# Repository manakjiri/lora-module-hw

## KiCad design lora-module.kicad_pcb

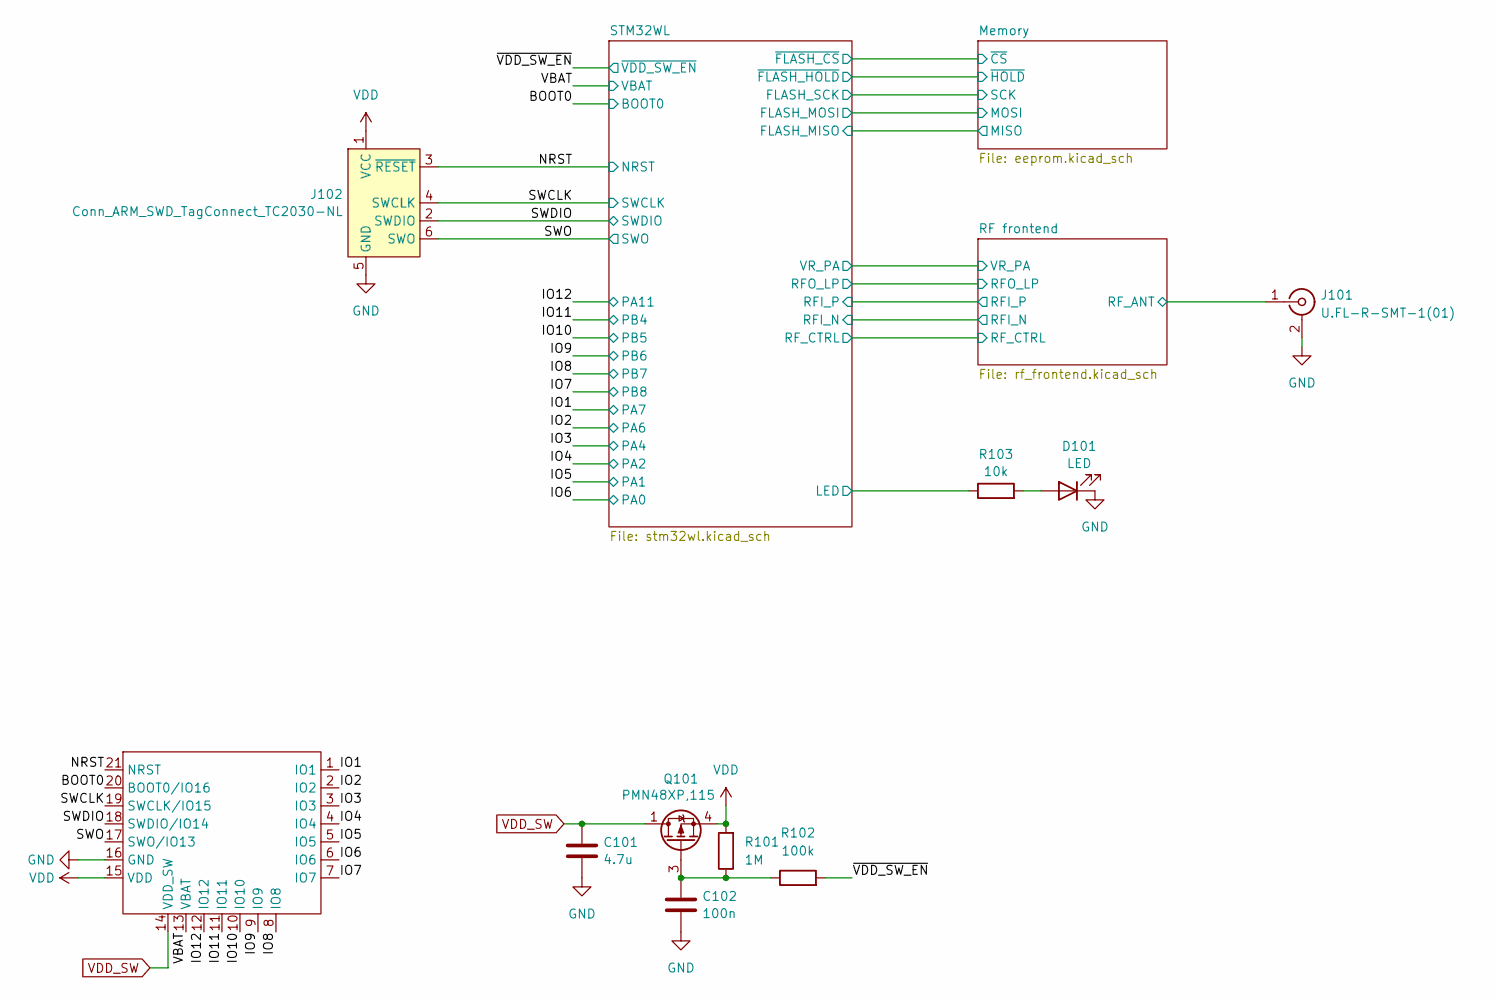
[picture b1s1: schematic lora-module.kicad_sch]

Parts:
C101: 4.7u; C_0603_1608Metric
C102: 100n; C_0402_1005Metric
D101: LED; LED_0402_1005Metric
J101: U.FL-R-SMT-1(01); U.FL_Hirose_U.FL-R-SMT-1_Vertical
J102: Conn_ARM_SWD_TagConnect_TC2030-NL; Tag-Connect_TC2030-IDC-NL_2x03_P1.27mm_Vertical
J106: module-connectors
Q101: PMN48XP,115; TSOP-6_1.65x3.05mm_P0.95mm
R101: 1M; R_0402_1005Metric
R102: 100k; R_0402_1005Metric
R103: 10k; R_0402_1005Metric

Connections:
/BOOT0: J106.20 (BOOT0/IO16); also elsewhere on the board
/IO1: J106.1 (IO1); also elsewhere on the board
/IO2: J106.2 (IO2); also elsewhere on the board
/IO3: J106.3 (IO3); also elsewhere on the board
/IO4: J106.4 (IO4); also elsewhere on the board
/IO5: J106.5 (IO5); also elsewhere on the board
/IO6: J106.6 (IO6); also elsewhere on the board
/IO7: J106.7 (IO7); also elsewhere on the board
/IO8: J106.8 (IO8); also elsewhere on the board
/IO9: J106.9 (IO9); also elsewhere on the board
/IO10: J106.10 (IO10); also elsewhere on the board
/IO11: J106.11 (IO11); also elsewhere on the board
/IO12: J106.12 (IO12); also elsewhere on the board
/NRST: J102.3 (~RESET), J106.21 (NRST); also elsewhere on the board
/RF frontend/RF_ANT: J101.1 (In); also elsewhere on the board
/STM32WL/LED: R103.1; also elsewhere on the board
/SWCLK: J102.4 (SWCLK), J106.19 (SWCLK/IO15); also elsewhere on the board
/SWDIO: J102.2 (SWDIO), J106.18 (SWDIO/IO14); also elsewhere on the board
/SWO: J102.6 (SWO), J106.17 (SWO/IO13); also elsewhere on the board
/VBAT: J106.13 (VBAT); also elsewhere on the board
/~VDD_SW_EN: R102.2; also elsewhere on the board
GND: C101.2, C102.2, D101.1 (K), J101.2 (Ext), J102.5 (GND), J106.16 (GND); also elsewhere on the board
unnamed: D101.2 (A), R103.2
unnamed: C102.1, Q101.3 (G), R101.1, R102.1
VDD: J102.1 (VCC), J106.15 (VDD), Q101.4 (S), R101.2; also elsewhere on the board
VDD_SW: C101.1, J106.14 (VDD_SW), Q101.1 (D), Q101.2 (D), Q101.5 (D), Q101.6 (D); also elsewhere on the board

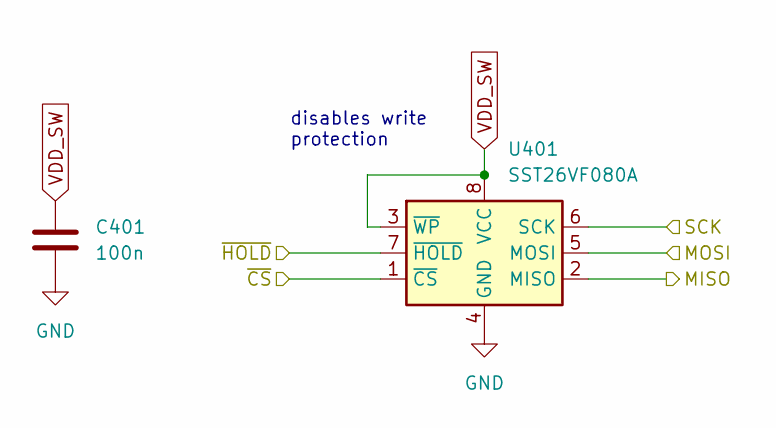
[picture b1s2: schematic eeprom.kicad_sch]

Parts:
C401: 100n; C_0402_1005Metric
U401: SST26VF080A; WDFN-8-1EP_6x5mm_P1.27mm_EP3.4x4mm

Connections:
/Memory/MISO: U401.2 (MISO); also elsewhere on the board
/Memory/MOSI: U401.5 (MOSI); also elsewhere on the board
/Memory/SCK: U401.6 (SCK); also elsewhere on the board
/Memory/~CS: U401.1 (~CS); also elsewhere on the board
/Memory/~HOLD: U401.7 (~HOLD); also elsewhere on the board
GND: C401.2, U401.4 (GND), U401.9 (GND); also elsewhere on the board
VDD_SW: C401.1, U401.3 (~WP), U401.8 (VCC); also elsewhere on the board

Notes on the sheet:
disables write protection

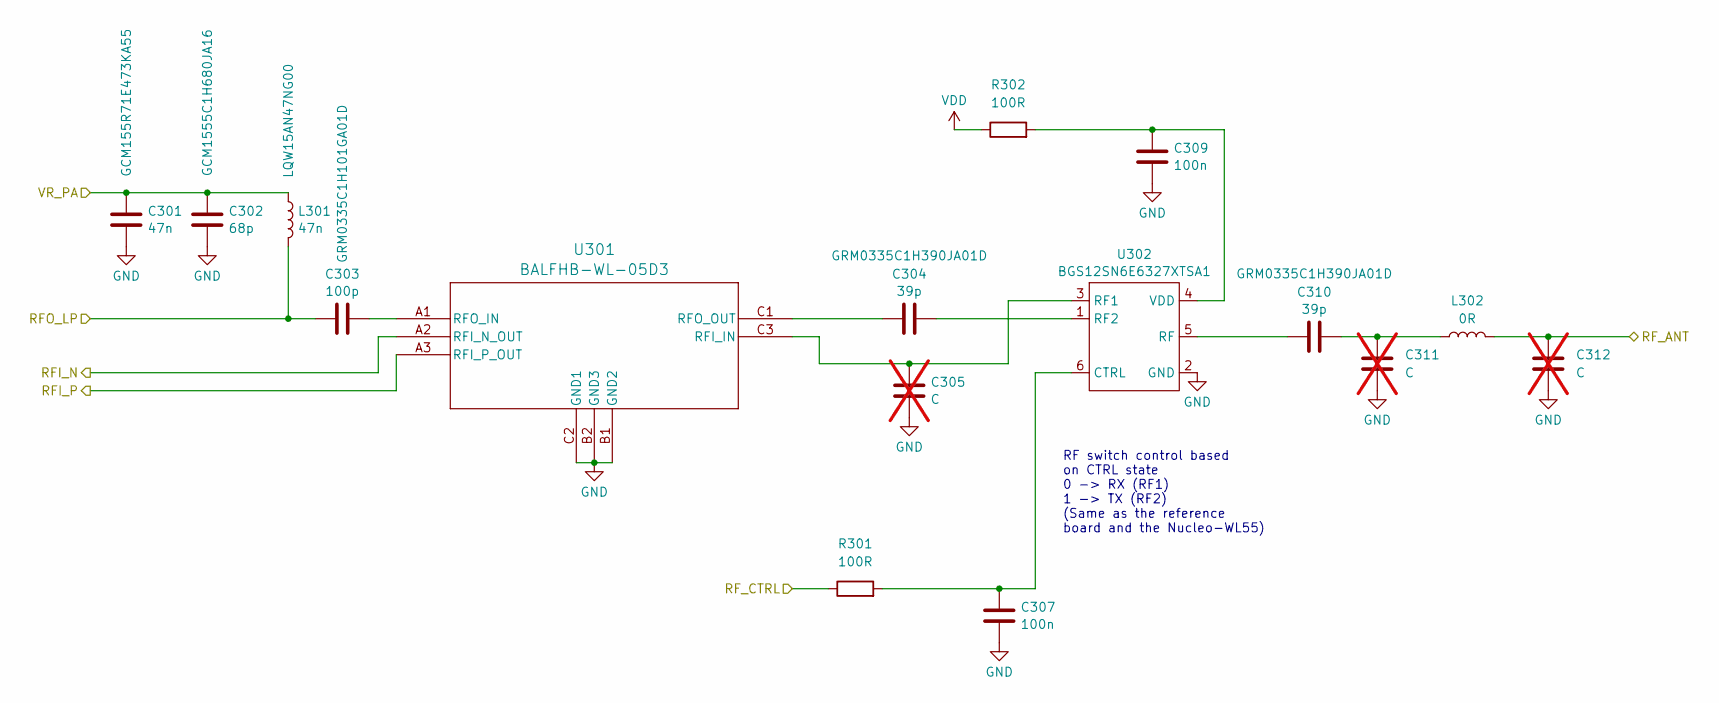
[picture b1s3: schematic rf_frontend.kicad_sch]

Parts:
C301: 47n; C_0603_1608Metric; Part GCM155R71E473KA55
C302: 68p; C_0402_1005Metric; Part GCM1555C1H680JA16
C303: 100p; C_0402_1005Metric; Part GRM0335C1H101GA01D
C304, C310: 39p; C_0402_1005Metric; Part GRM0335C1H390JA01D
C305, C311, C312: C; C_0402_1005Metric_Pad0.74x0.62mm_HandSolder; not fitted
C307, C309: 100n; C_0402_1005Metric
L301: 47n; L_0402_1005Metric; Part LQW15AN47NG00
L302: 0R; L_0402_1005Metric_Pad0.77x0.64mm_HandSolder
R301, R302: 100R; R_0402_1005Metric
U301: BALFHB-WL-05D3; BGA8_BALFHB_STM
U302: BGS12SN6E6327XTSA1; Infineon_PG-TSNP-6-10_0.7x1.1mm_0.7x1.1mm_P0.4mm

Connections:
/RF frontend/RFI_N: U301.A2 (RFI_N_OUT); also elsewhere on the board
/RF frontend/RFI_P: U301.A3 (RFI_P_OUT); also elsewhere on the board
/RF frontend/RFO_LP: C303.1, L301.2; also elsewhere on the board
/RF frontend/RF_ANT: C312.1, L302.2; also elsewhere on the board
/RF frontend/RF_CTRL: R301.1; also elsewhere on the board
/RF frontend/VR_PA: C301.1, C302.1, L301.1; also elsewhere on the board
GND: C301.2, C302.2, C305.2, C307.2, C309.2, C311.2, C312.2, U301.B1 (GND2), U301.B2 (GND3), U301.C2 (GND1), U302.2 (GND); also elsewhere on the board
unnamed: C310.2, C311.1, L302.1
unnamed: C305.1, U301.C3 (RFI_IN), U302.3 (RF1)
unnamed: C303.2, U301.A1 (RFO_IN)
unnamed: C304.1, U301.C1 (RFO_OUT)
unnamed: C307.1, R301.2, U302.6 (CTRL)
unnamed: C304.2, U302.1 (RF2)
unnamed: C310.1, U302.5 (RF)
unnamed: C309.1, R302.2, U302.4 (VDD)
VDD: R302.1; also elsewhere on the board

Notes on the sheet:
RF switch control based on CTRL state 0 -> RX (RF1) 1 -> TX (RF2) (Same as the reference board and the Nucleo-WL55)

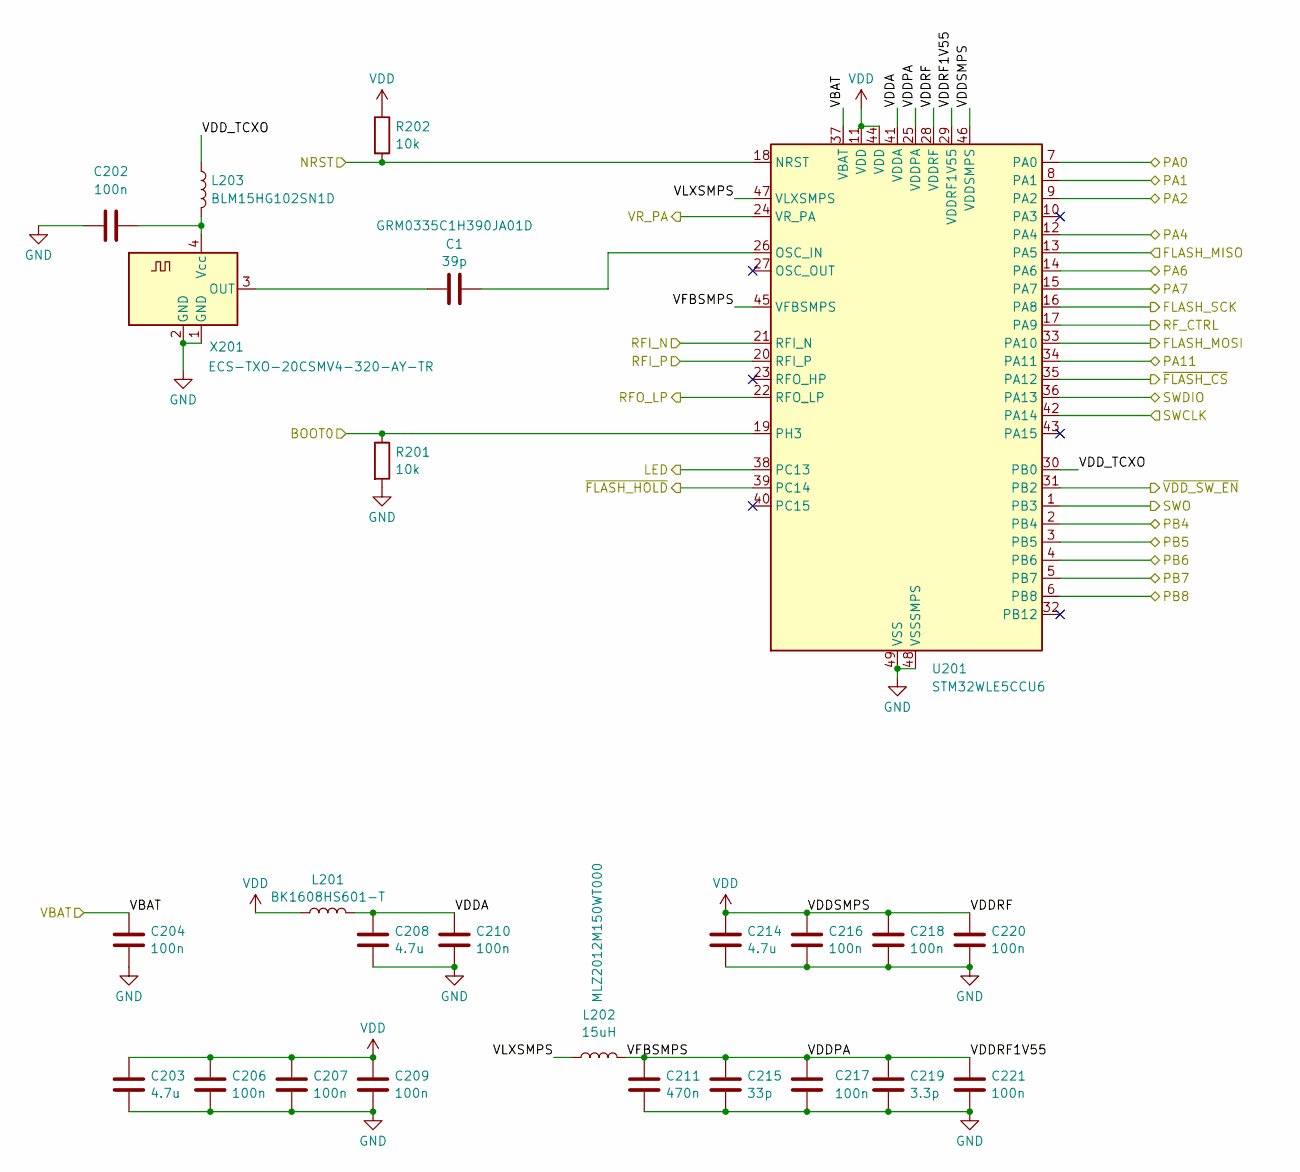
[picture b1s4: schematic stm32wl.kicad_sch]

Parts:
C1: 39p; C_0402_1005Metric; Part GRM0335C1H390JA01D
C202, C204, C206, C207, C209, C210, C216, C217, C218, C220, C221: 100n; C_0402_1005Metric
C203, C208, C214: 4.7u; C_0603_1608Metric
C211: 470n; C_0603_1608Metric
C215: 33p; C_0402_1005Metric
C219: 3.3p; C_0402_1005Metric
L201: BK1608HS601-T; L_0603_1608Metric
L202: 15uH; L_0805_2012Metric; Part MLZ2012M150WT000
L203: BLM15HG102SN1D; L_0402_1005Metric
R201, R202: 10k; R_0402_1005Metric
U201: STM32WLE5CCU6; QFN-48-1EP_7x7mm_P0.5mm_EP5.6x5.6mm
X201: ECS-TXO-20CSMV4-320-AY-TR; NX2016SA_NDK

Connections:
/BOOT0: R201.1, U201.19 (PH3); also elsewhere on the board
/IO1: U201.15 (PA7); also elsewhere on the board
/IO2: U201.14 (PA6); also elsewhere on the board
/IO3: U201.12 (PA4); also elsewhere on the board
/IO4: U201.9 (PA2); also elsewhere on the board
/IO5: U201.8 (PA1); also elsewhere on the board
/IO6: U201.7 (PA0); also elsewhere on the board
/IO7: U201.6 (PB8); also elsewhere on the board
/IO8: U201.5 (PB7); also elsewhere on the board
/IO9: U201.4 (PB6); also elsewhere on the board
/IO10: U201.3 (PB5); also elsewhere on the board
/IO11: U201.2 (PB4); also elsewhere on the board
/IO12: U201.34 (PA11); also elsewhere on the board
/Memory/MISO: U201.13 (PA5); also elsewhere on the board
/Memory/MOSI: U201.33 (PA10); also elsewhere on the board
/Memory/SCK: U201.16 (PA8); also elsewhere on the board
/Memory/~CS: U201.35 (PA12); also elsewhere on the board
/Memory/~HOLD: U201.39 (PC14); also elsewhere on the board
/NRST: R202.2, U201.18 (NRST); also elsewhere on the board
/RF frontend/RFI_N: U201.21 (RFI_N); also elsewhere on the board
/RF frontend/RFI_P: U201.20 (RFI_P); also elsewhere on the board
/RF frontend/RFO_LP: U201.22 (RFO_LP); also elsewhere on the board
/RF frontend/RF_CTRL: U201.17 (PA9); also elsewhere on the board
/RF frontend/VR_PA: U201.24 (VR_PA); also elsewhere on the board
/STM32WL/LED: U201.38 (PC13); also elsewhere on the board
/STM32WL/VDDA: C208.1, C210.1, L201.2, U201.41 (VDDA)
/STM32WL/VDDPA: C211.1, C215.1, C217.1, C219.1, C221.1, L202.2, U201.25 (VDDPA), U201.29 (VDDRF1V55), U201.45 (VFBSMPS)
/STM32WL/VDD_TCXO: L203.1, U201.30 (PB0)
/STM32WL/VLXSMPS: L202.1, U201.47 (VLXSMPS)
/SWCLK: U201.42 (PA14); also elsewhere on the board
/SWDIO: U201.36 (PA13); also elsewhere on the board
/SWO: U201.1 (PB3); also elsewhere on the board
/VBAT: C204.1, U201.37 (VBAT); also elsewhere on the board
/~VDD_SW_EN: U201.31 (PB2); also elsewhere on the board
GND: C202.1, C203.2, C204.2, C206.2, C207.2, C208.2, C209.2, C210.2, C211.2, C214.2, C215.2, C216.2, C217.2, C218.2, C219.2, C220.2, C221.2, R201.2, U201.48 (VSSSMPS), U201.49 (VSS), X201.1 (GND), X201.2 (GND); also elsewhere on the board
unnamed: C1.2, U201.26 (OSC_IN)
unnamed: C1.1, X201.3 (OUT)
unnamed: C202.2, L203.2, X201.4 (Vcc)
VDD: C203.1, C206.1, C207.1, C209.1, C214.1, C216.1, C218.1, C220.1, L201.1, R202.1, U201.11 (VDD), U201.28 (VDDRF), U201.44 (VDD), U201.46 (VDDSMPS); also elsewhere on the board

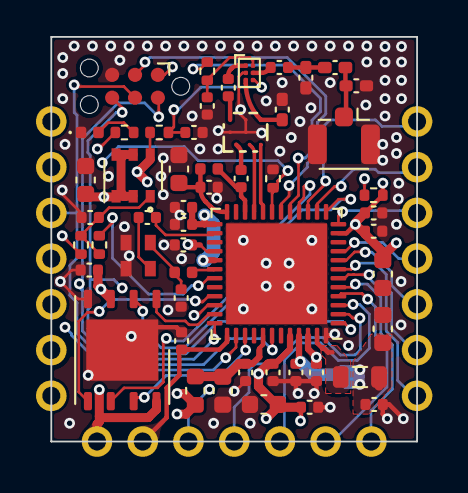
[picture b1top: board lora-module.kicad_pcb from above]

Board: 4 copper layers, 20.3 x 22.5 mm, 53 parts (0 on the bottom side), 51 nets.

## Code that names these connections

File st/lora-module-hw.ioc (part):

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Mcu.Name=STM32WLE5CCUx
Mcu.Package=UFQFPN48
Mcu.UserName=STM32WLE5CCUx
PA1.Mode=Full_Duplex_Master
PA1.Signal=SPI1_SCK
PA10.Mode=Full_Duplex_Master
PA10.Signal=SPI2_MOSI
PA12.GPIOParameters=GPIO_Label
PA12.GPIO_Label=FLASH_CS
PA12.Signal=GPIO_Output
PA13.Mode=Trace_Asynchronous_SW
PA13.Signal=DEBUG_JTMS-SWDIO
PA14.Mode=Trace_Asynchronous_SW
PA14.Signal=DEBUG_JTCK-SWCLK
PA5.Mode=Full_Duplex_Master
PA5.Signal=SPI2_MISO
PA8.Mode=Full_Duplex_Master
PA8.Signal=SPI2_SCK
PA9.GPIOParameters=GPIO_Label
PA9.GPIO_Label=RF_CTRL
PA9.Signal=GPIO_Output
PB0-VDD_TCXO.Mode=HSE-TCXO
PB0-VDD_TCXO.Signal=VDDTCXO
PB2.GPIOParameters=GPIO_Label
PB2.GPIO_Label=CDD_SW_NEN
PB2.Signal=GPIO_Output
PB3.Mode=Trace_Asynchronous_SW
PB3.Signal=DEBUG_JTDO-SWO
PB4.Mode=Full_Duplex_Master
PB4.Signal=SPI1_MISO
PB5.Mode=Full_Duplex_Master
PB5.Signal=SPI1_MOSI
PB7.Signal=I2C1_SDA
PB8.Signal=I2C1_SCL
PC13.GPIOParameters=GPIO_Label
PC13.GPIO_Label=LED_EN
PC13.Signal=GPIO_Output
PC14-OSC32_IN.GPIOParameters=GPIO_Label
PC14-OSC32_IN.GPIO_Label=FLASH_HOLD
PC14-OSC32_IN.Signal=GPIO_Output
RCC.HSE_VALUE=32000000
RCC.SYSCLKFreq_VALUE=48000000
RCC.SYSCLKSource=RCC_SYSCLKSOURCE_PLLCLK
board=custom

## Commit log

2023-10-14 working on the RF frontend
2023-10-15 STM power mostly done
2023-10-17 added cubemx file for checking pinout
2023-10-18 most components placed, routed the RF section
2023-10-19 most of the components are placed
2023-10-19 added tag-connect and a led, noticed i forgot a crystal
2023-10-19 added the crystal
2023-10-20 added castellated edge connectors
2023-10-20 created a footprint for the edge connectors
2023-10-22 mostly finishing, all IOs connected, drc clean
2023-10-22 added teardrops, finishing touches
2023-10-23 added bottom silkscreen
2023-10-26 groundplane settings tweak
2023-10-26 batter layout of the SMPS section
2023-10-28 bom tweaks
2023-11-27 hw: after manufacturing
2024-03-02 stm32cubeide project for cross-checking
2024-03-07 changed XO to TCXO
2024-03-08 small tweaks
2024-03-26 ioc update
2024-03-26 module pinout change
2024-03-26 bom update and other tweaks
